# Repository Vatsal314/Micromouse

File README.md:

# MicroMouse: Autonomous Maze-Solving Robot

An autonomous, self-navigating maze-solving robot designed to map, compute, and solve a grid using the Flood Fill algorithm. The system features a custom-designed PCB to streamline power and sensing, coupled with real-time sensor feedback over standard serial protocols.  

## Tech Stack & Hardware Components
- Microcontroller: STM32F411CEU6 "Black Pill" (ARM Cortex-M4)
- Core Algorithm: Flood Fill (Maze mapping, cell weight updates, and path optimization)
- Sensing & Telemetry: 
  - VL53L0X Time-of-Flight (ToF) sensors for precise distance/wall detection
  - MPU6050 Gyroscope/Accelerometer for straight-line stabilization and precise turns
- Actuation & Control: 
  - 12V 1000RPM N20 Encoder Motors for closed-loop speed control
  - TB6612FNG Dual Motor Driver
- Power Management: 11.1V LiPo battery pack with onboard regulation for logic and motor rails
- Design Tools: KiCad (Schematics & PCB Layout)

## Firmware & Logic Implementation
- Maze Solving: Implements a dynamic Flood Fill matrix routine that updates cell values on the fly as the mouse discovers walls.
- Hardware Integration: Configured SPI/I2C buses to communicate with peripheral sensors and motor drivers, ensuring low-latency feedback loops for precise alignment.

## Hardware Architecture & PCB Design
To minimize structural footprint and eliminate complex wiring failure points, a custom multi-layer PCB was fabricated.
- Power Management: Dedicated onboard regulation filtering out 12V motor noise from the sensitive 3.3V STM32 logic lines.
- Sensor Alignment: Precise angled placement for the VL53L0X ToF sensors to map front and side clearances accurately.

## Maze Description
The robot was tested and validated in a physical maze environment configured with the following specifications:
- Dimensions and Grid: A modular grid layout featuring distinct pathways, vertical wall dividers, and an enclosed central target zone.
- Physical Construction: Built using white foam board panels for the structural walls and a gridded base layer featuring blue alignment markings to delineate cell thresholds.
- Core Objective: The robot starts from the outer perimeter and relies on real-time sensory feedback to dynamically map cell paths, track orientation changes, and navigate toward the centralized goal area.

- 

## Algorithm & Firmware Implementation

The robot utilizes a dynamic Flood Fill algorithm optimized for real-time maze-mapping, tracking orientation updates, path optimization, and execute routines.

### 1. Maze Initialization (Flood Fill Array)
- **Manhattan Distance Matrix:** At startup, the `initFloodfill` routine populates the `arena_map` grid using Manhattan distance bounds calculated relative to the target cell coordinate `(0, length - 1)`. Every cell is given an initial cost matrix weight indicating its theoretical steps away from the destination.
- **Perimeter Boundary Flagging:** The `initWalls` function instantiates the initial maze boundary configuration, defaulting the grid's outer boundary elements to closed parameters.

### 2. Sensor Polling & Real-Time Mapping
- **Dynamic Wall Updating:** During runtime execution loop, the robot polls data from the left, right, and center VL53L0X Time-of-Flight (ToF) sensors. If an obstacle distance drops below `detectDist` (180 mm), the corresponding coordinate index within the global `wall_data` matrix is permanently flagged (`= 1`).
- **Orientation-Aware Bitmasking:** The code tracks the absolute heading (`facing` variable mapping to 0: West, 1: North, 2: East, 3: South). Relative ToF configurations (Left, Front, Right) are translated into absolute compass coordinates to ensure accurate wall updates as the orientation shifts.

### 3. Queue-Driven Map Restructuring (`rearrange_map`)
- **Dead-End Discovery:** If the robot discovers new walls that make its current cell value equal to or lower than all accessible adjacent neighbors, the `rearrange_map` routine initiates.
- **BFS Flood Refresh:** The cell coordinate is pushed onto a custom `Queue` structure. The program continuously pops elements from the queue, calculating the minimum accessible neighbor via `minimum_value_accessible_neighbors`. The cell value is updated dynamically to `smallest_neighbor_value + 1`, and all unblocked adjacent neighbors are placed into the queue to recursively refresh the local routing map.

### 4. Navigation & Path Optimization
- **Compass to Action Translation:** The system determines optimal cell transitions through the `direction_wrt_bot` routine. It converts required compass steps into actual motion commands (`moveForward`, `TurnLeft`, `TurnRight`, `Turn180`).
- **Stack-Based Path Reduction:** As the mouse explores the maze, it tracks steps sequentially inside `path_taken`. Dead ends or backtracks are parsed by `reduceDirections`, which processes the path string through a custom stack interface to discard inverse direction pairings (e.g., North-South or East-West cancellations). This converts the discovery track into a clean tracking coordinate sequence saved into `short_path`.

### 5. Acceleration-Optimized Final Run (`final_run`)
- After mapping out the optimal trajectory, the system executes a localized final straightaway acceleration routine via `final_run`. 
- Instead of stopping at every single node intersection, the algorithm aggregates sequential straight moves (`steps++`). If sequential cells follow a uniform direction, it executes long-distance acceleration (`moveForward(steps * steplength * 0.9)`) coupled with tuned PD constants (`KP_WALL`, `KD_WALL`, `KP_YAW`), leveraging the N20 encoders for high-speed transit.

## Hardware Design & PCB Layout

### Schematic Capture

### PCB Layout & Routing

> **Note on Hardware Evolution:** This custom multi-layer PCB was originally architected and routed around a Teensy 4.1 MCU footprint. The subsequent physical implementation and final firmware integration were ported to the STM32F411CEU6 "Black Pill" microcontroller to align with specific processing, layout, and peripheral subsystem constraints.

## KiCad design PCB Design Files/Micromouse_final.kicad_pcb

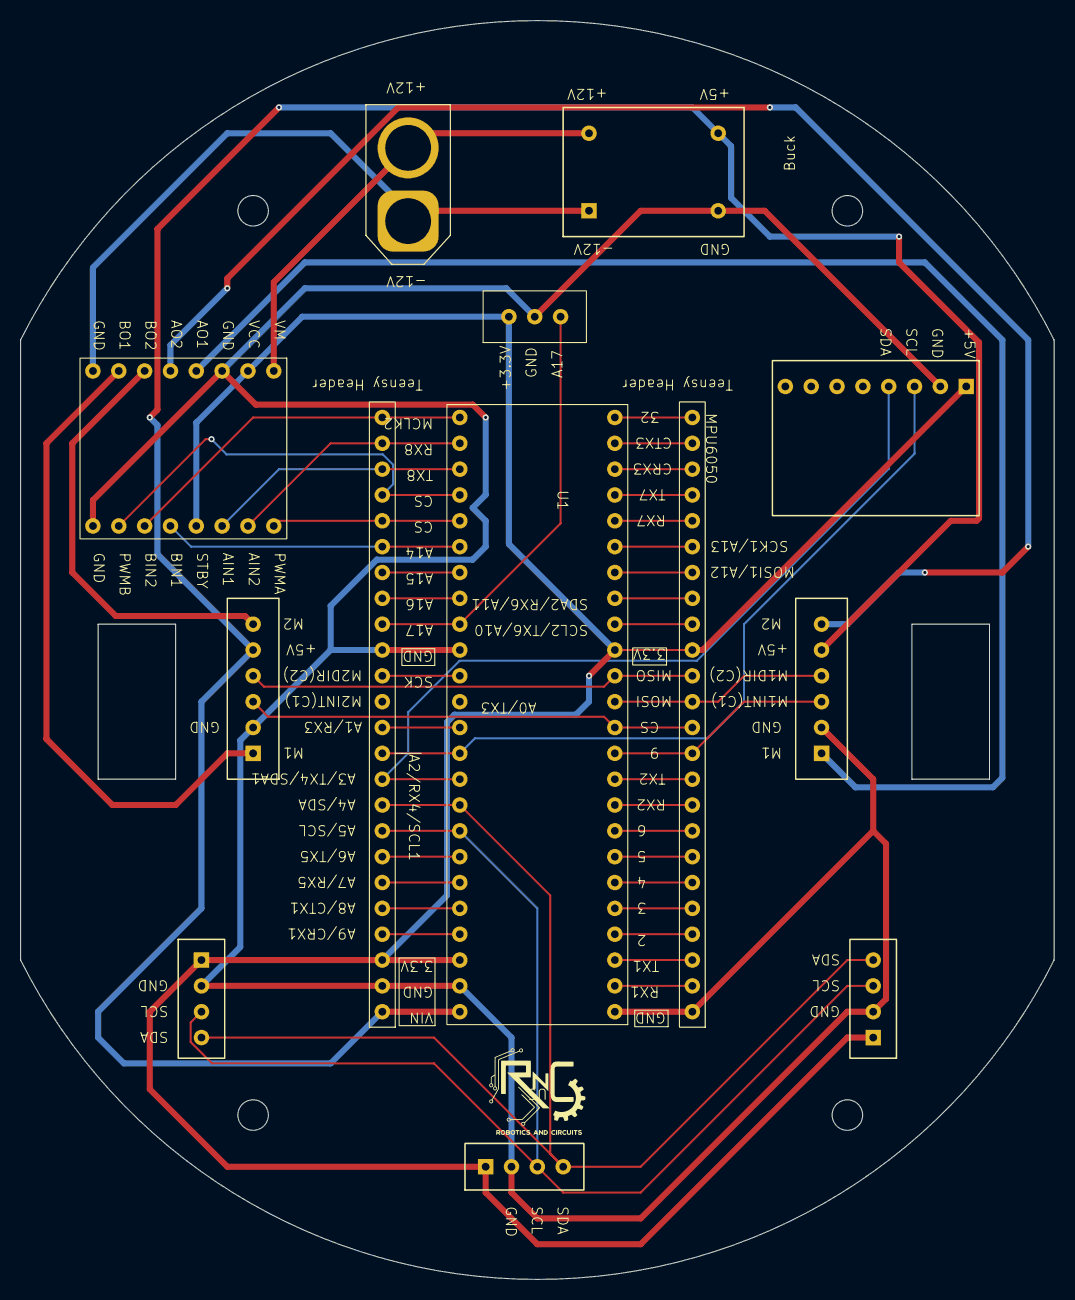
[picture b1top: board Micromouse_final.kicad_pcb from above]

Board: 2 copper layers, 101.6 x 123.8 mm, 13 parts (0 on the bottom side), 49 nets.

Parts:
M1: Motor_Encoder_1; Encoder
M2: Motor_Encoder_2; Encoder
TOF_1, TOF_2, TOF_3: VL53L0X TOF; TOF sensor
U1: Tb6612FNG; TB6612FNG
U2, U7: Teensy headers
U3: BUCK
U4: AMASS_XT60-F_1x02_P7.20mm_Vertical
U5: Teensy_4.1
U6: SPDT_micromouse
U8: MPU-6050 GYRO; MPU6050

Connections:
+3.3V: TOF_1.1 (VIN), TOF_2.1 (VIN), TOF_3.1 (VIN), U1.2 (VCC), U1.13 (STBY), U2.15 (3.3V), U5.15 (3.3V), U5.46 (3.3V), U6.1 (+5V), U7.3 (3.3V), U8.1 (VCC)
+5V: M1.5, M2.5, U3.3 (+5V), U5.48 (VIN), U7.1 (VIN)
+12V: U1.1 (VM), U3.1 (+12V), U4.1 (+12V)
-12V: U1.8 (GND_2), U3.2 (-12V), U4.2 (-12V)
A0: U5.36 (A0), U7.13 (A0)
A1: U5.37 (A1), U7.12 (A1)
A6: U5.42 (A6), U7.7 (A6)
A7: U5.43 (A7), U7.6 (A7)
A8: U5.44 (A8), U7.5 (A8)
A9: U5.45 (A9), U7.4 (A9)
A13: U2.19 (A13), U5.19 (A13)
A15: U5.31 (A15), U7.18 (A15)
A16: U5.32 (A16), U7.17 (A16)
A17: U5.33 (A17), U6.3 (DIGI), U7.16 (A17)
BCLK2: U2.6 (BCLK2), U5.6 (BCLK2)
CRX3: U2.22 (CRX3), U5.22 (CRX3)
CTX3: U2.23 (CTX3), U5.23 (CTX3)
GND: M1.2, M2.2, TOF_1.2 (GND), TOF_2.2 (GND), TOF_3.2 (GND), U1.3 (GND_1), U1.9 (GND_3), U2.1 (GND), U3.4 (GND), U5.1 (GND), U5.34 (GND), U5.47 (GND), U6.2 (GND), U7.2 (GND), U7.15 (GND), U8.2 (GND)
IN2: U2.7 (IN2), U5.7 (IN2)
LRCKL2: U2.5 (LRCLK2), U5.5 (LRCLK2)
M1DIR: M1.4, U2.13 (MOSI), U5.13 (MOSI)
M1IN1: U1.14 (AIN1), U5.27 (TX8), U7.22 (TX8)
M1IN2: U1.15 (AIN2), U5.26 (RX8), U7.23 (RX8)
M1INT: M1.3, U2.11 (OUT1C), U5.11 (OUT1C)
M1NEG: M1.6, U1.5 (A02)
M1POS: M1.1, U1.4 (A01)
M1PWM: U1.16 (PWMA), U5.29 (CS), U7.20 (CS)
M2DIR: M2.4, U2.14 (MIS), U5.14 (MIS)
M2IN1: U1.12 (BIN1), U5.30 (A14), U7.19 (a14)
M2IN2: U1.11 (BIN2), U5.25 (MCLK2), U7.24 (MCLK2)
M2INT: M2.3, U2.12 (MQSR), U5.12 (MQSR)
M2NEG: M2.6, U1.6 (B02)
M2POS: M2.1, U1.7 (B01)
M2PWM: U1.10 (PWMB), U5.28 (CS), U7.21 (CS)
MOSI1: U2.18 (MOSI1), U5.18 (MOSI1)
OUT1B: U2.24 (OUT1B), U5.24 (OUT1B)
OUT2: U2.4 (OUT2), U5.4 (OUT2)
RX1: U2.2 (RX1), U5.2 (RX1)
RX7: U2.20 (RX7), U5.20 (RX7)
SCK: U5.35 (SCK), U7.14 (SCK)
SCL: TOF_1.3 (SCL), TOF_2.3 (SCL), TOF_3.3 (SCL), U5.38 (A2), U5.41 (A5), U7.8 (A5), U7.11 (A2), U8.3 (SCL)
SCL2: U2.16 (SCL2), U5.16 (SCL2)
SDA: TOF_1.4 (SDA), TOF_2.4 (SDA), TOF_3.4 (SDA), U5.39 (A3), U5.40 (A4), U7.9 (A4), U7.10 (A3), U8.4 (SDA)
SDA2: U2.17 (SDA2), U5.17 (SDA2)
TX1: U2.3 (TX1), U5.3 (TX1)
TX7: U2.21 (TX7), U5.21 (TX7)
XSHUT_TOF1: U2.8 (OUT1D), U5.8 (OUT1D)
XSHUT_TOF2: U2.9 (OUT1A), U5.9 (OUT1A)
XSHUT_TOF3: U2.10 (IN1), U5.10 (IN1)
